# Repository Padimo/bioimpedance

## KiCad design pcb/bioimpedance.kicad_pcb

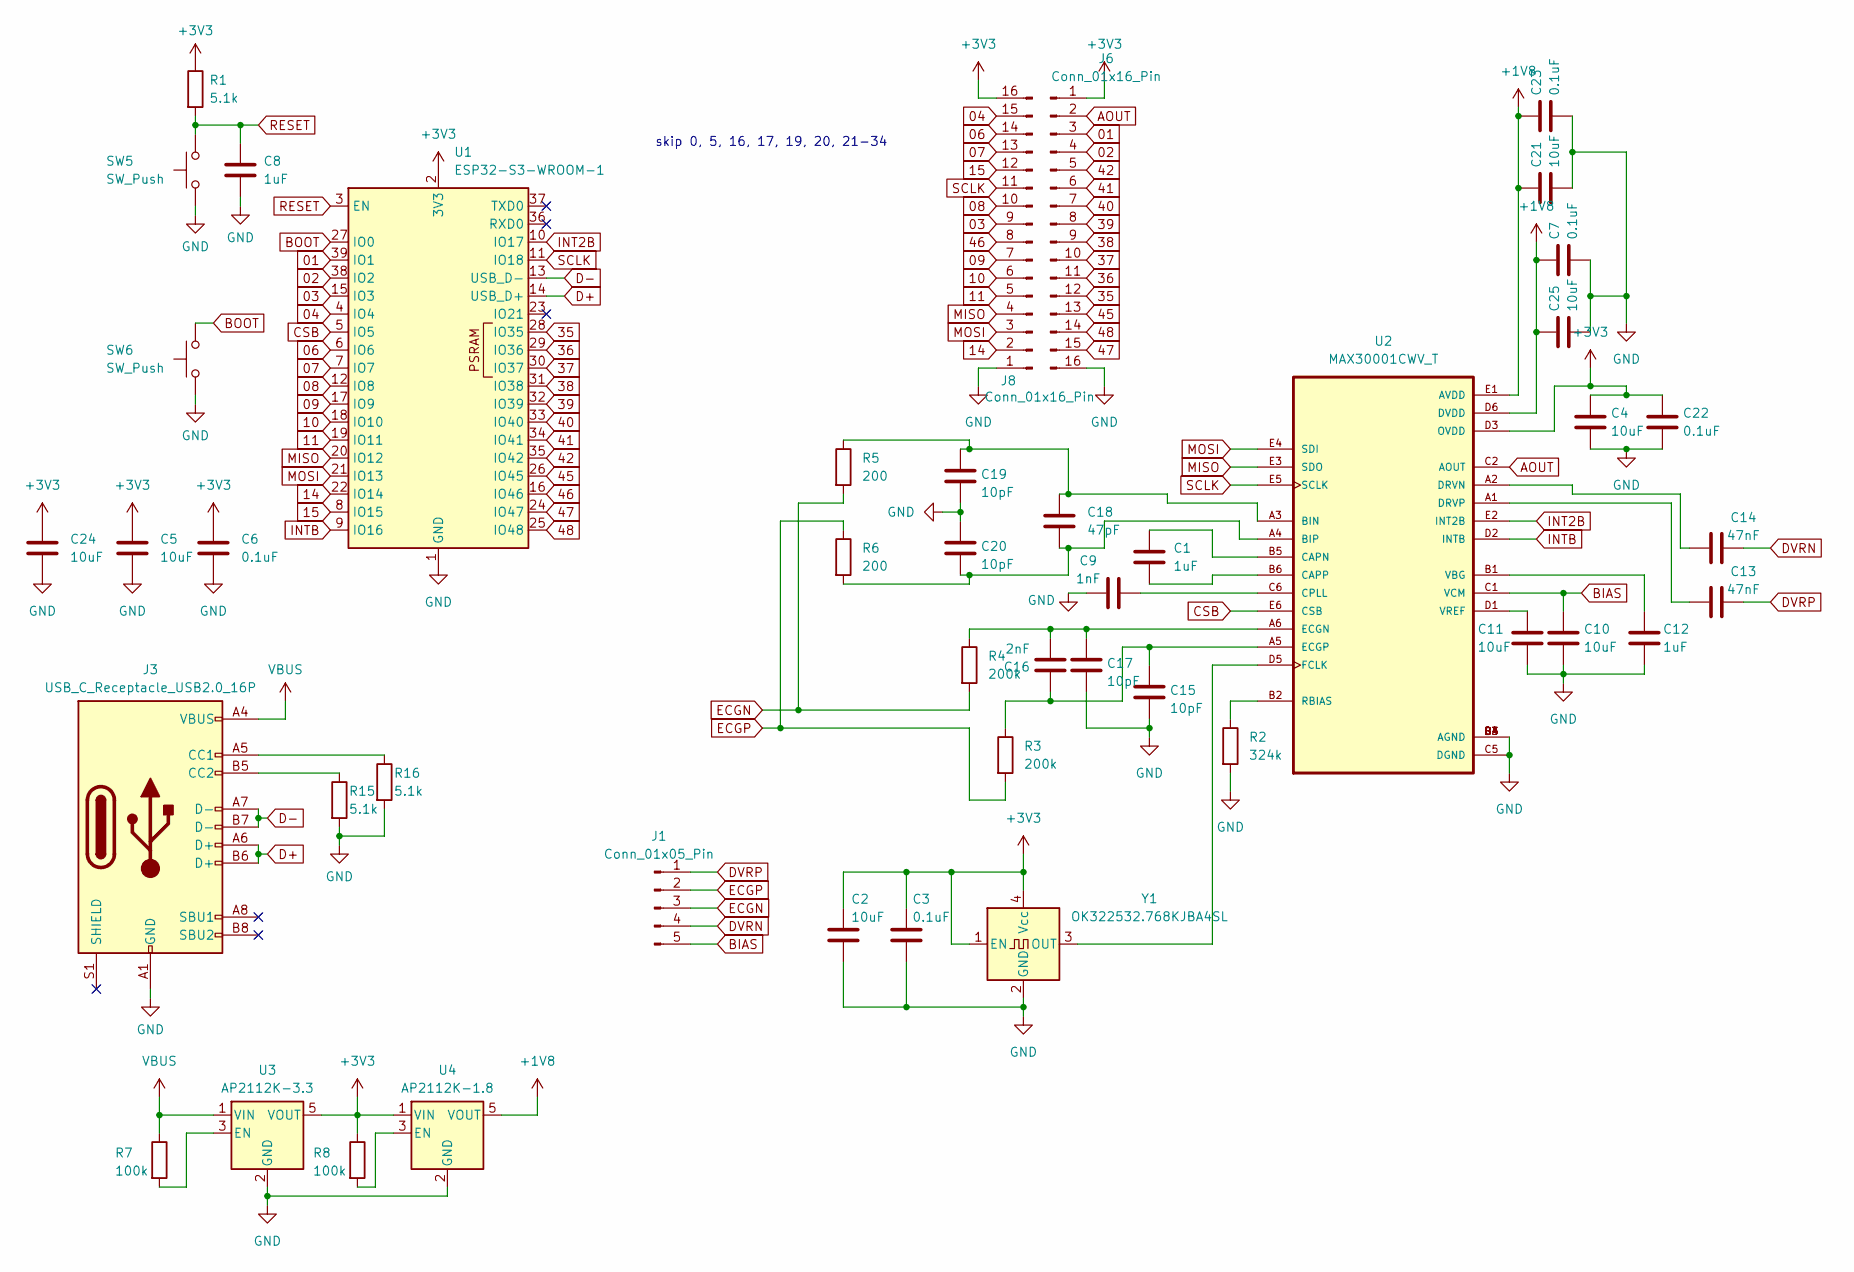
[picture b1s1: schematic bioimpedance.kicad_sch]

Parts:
C1, C8, C12: 1uF; C_0805_2012Metric
C2, C4, C5, C10, C11, C21, C24, C25: 10uF; C_0805_2012Metric
C3, C6, C7, C22, C23: 0.1uF; C_0805_2012Metric
C9: 1nF; C_0805_2012Metric
C13, C14: 47nF; C_0805_2012Metric
C15, C17, C19, C20: 10pF; C_0805_2012Metric
C16: 2nF; C_0805_2012Metric
C18: 47pF; C_0805_2012Metric
J1: Conn_01x05_Pin; PinHeader_1x05_P2.54mm_Vertical
J3: USB_C_Receptacle_USB2.0_16P; USB_C_Receptacle_GCT_USB4085
J6, J8: Conn_01x16_Pin; PinHeader_1x16_P2.54mm_Vertical
R1, R15, R16: 5.1k; R_0805_2012Metric
R2: 324k; R_0805_2012Metric
R3, R4: 200k; R_0805_2012Metric
R5, R6: 200; R_0805_2012Metric
R7, R8: 100k; R_0805_2012Metric
SW5, SW6: SW_Push; SW_Push_1P1T_NO_CK_KSC6xxJ
U1: ESP32-S3-WROOM-1
U2: MAX30001CWV_T; BGA30N50P5X6_274X292X69N
U3: AP2112K-3.3; SOT-23-5
U4: AP2112K-1.8; SOT-23-5
Y1: OK322532.768KJBA4SL; Crystal_SMD_3225-4Pin_3.2x2.5mm

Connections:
01: J6.3, U1.39 (IO1)
02: J6.4, U1.38 (IO2)
03: J8.9, U1.15 (IO3)
04: J8.15, U1.4 (IO4)
06: J8.14, U1.6 (IO6)
07: J8.13, U1.7 (IO7)
08: J8.10, U1.12 (IO8)
09: J8.7, U1.17 (IO9)
10: J8.6, U1.18 (IO10)
11: J8.5, U1.19 (IO11)
14: J8.2, U1.22 (IO14)
15: J8.12, U1.8 (IO15)
35: J6.12, U1.28 (IO35)
36: J6.11, U1.29 (IO36)
37: J6.10, U1.30 (IO37)
38: J6.9, U1.31 (IO38)
39: J6.8, U1.32 (IO39)
40: J6.7, U1.33 (IO40)
41: J6.6, U1.34 (IO41)
42: J6.5, U1.35 (IO42)
45: J6.13, U1.26 (IO45)
46: J8.8, U1.16 (IO46)
47: J6.15, U1.24 (IO47)
48: J6.14, U1.25 (IO48)
+1V8: C7.1, C21.1, C23.1, C25.1, U2.D6 (DVDD), U2.E1 (AVDD), U4.5 (VOUT)
+3V3: C2.1, C3.1, C4.1, C5.1, C6.1, C22.1, C24.1, J6.1, J8.16, R1.1, R8.1, U1.2 (3V3), U2.D3 (OVDD), U3.5 (VOUT), U4.1 (VIN), Y1.1 (EN), Y1.4 (Vcc)
AOUT: J6.2, U2.C2 (AOUT)
BIAS: C10.1, J1.5, U2.C1 (VCM)
BOOT: SW6.2, U1.27 (IO0)
CSB: U1.5 (IO5), U2.E6 (CSB)
D+: J3.A6 (D+), J3.B6 (D+), U1.14 (USB_D+)
D-: J3.A7 (D-), J3.B7 (D-), U1.13 (USB_D-)
DVRN: C14.2, J1.4
DVRP: C13.2, J1.1
ECGN: J1.3, R4.2, R5.2
ECGP: J1.2, R3.2, R6.1
GND: C2.2, C3.2, C4.2, C5.2, C6.2, C7.2, C8.2, C9.1, C10.2, C11.2, C12.2, C15.2, C17.2, C19.2, C20.1, C21.2, C22.2, C23.2, C24.2, C25.2, J3.A1 (GND), J3.A12 (GND), J3.B1 (GND), J3.B12 (GND), J6.16, J8.1, R2.2, R15.2, R16.2, SW5.1, SW6.1, U1.1 (GND), U1.40 (GND), U1.41 (GND), U2.B3 (AGND), U2.B4 (AGND), U2.C3 (AGND), U2.C4 (AGND), U2.C5 (DGND), U2.D4 (AGND), U3.2 (GND), U4.2 (GND), Y1.2 (GND)
INT2B: U1.10 (IO17), U2.E2 (INT2B)
INTB: U1.9 (IO16), U2.D2 (INTB)
MISO: J8.4, U1.20 (IO12), U2.E3 (SDO)
MOSI: J8.3, U1.21 (IO13), U2.E4 (SDI)
unnamed: J3.A5 (CC1), R16.1
unnamed: J3.B5 (CC2), R15.1
unnamed: C18.1, C19.1, R5.1, U2.A3 (BIN)
unnamed: C18.2, C20.2, R6.2, U2.A4 (BIP)
unnamed: C1.1, U2.B5 (CAPN)
unnamed: C1.2, U2.B6 (CAPP)
unnamed: C9.2, U2.C6 (CPLL)
unnamed: C14.1, U2.A2 (DRVN)
unnamed: C13.1, U2.A1 (DRVP)
unnamed: C16.2, C17.1, R4.1, U2.A6 (ECGN)
unnamed: C15.1, C16.1, R3.1, U2.A5 (ECGP)
unnamed: U2.D5 (FCLK), Y1.3 (OUT)
unnamed: R2.1, U2.B2 (RBIAS)
unnamed: C12.1, U2.B1 (VBG)
unnamed: C11.1, U2.D1 (VREF)
unnamed: R7.2, U3.3 (EN)
unnamed: R8.2, U4.3 (EN)
RESET: C8.1, R1.2, SW5.2, U1.3 (EN)
SCLK: J8.11, U1.11 (IO18), U2.E5 (SCLK)
VBUS: J3.A4 (VBUS), J3.A9 (VBUS), J3.B4 (VBUS), J3.B9 (VBUS), R7.1, U3.1 (VIN)

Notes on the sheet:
skip 0, 5, 16, 17, 19, 20, 21-34

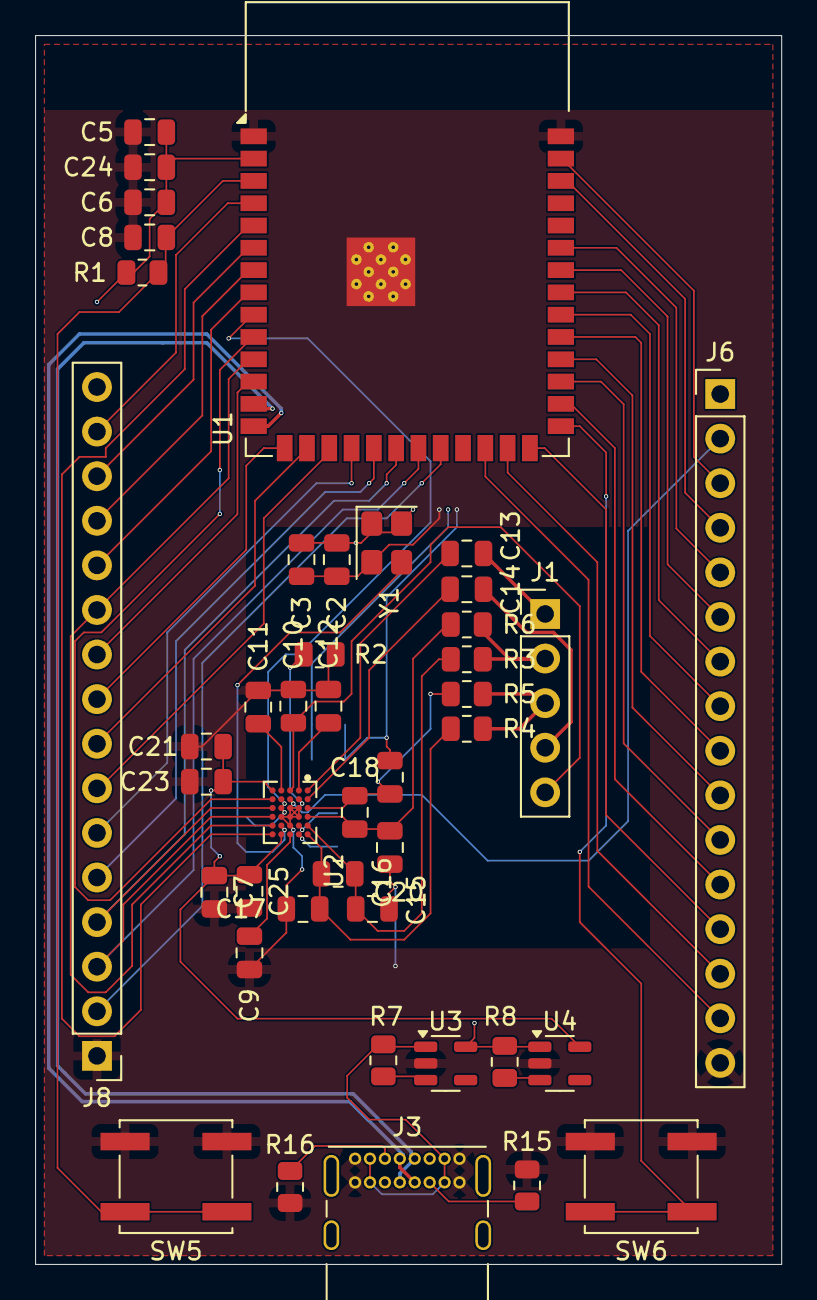
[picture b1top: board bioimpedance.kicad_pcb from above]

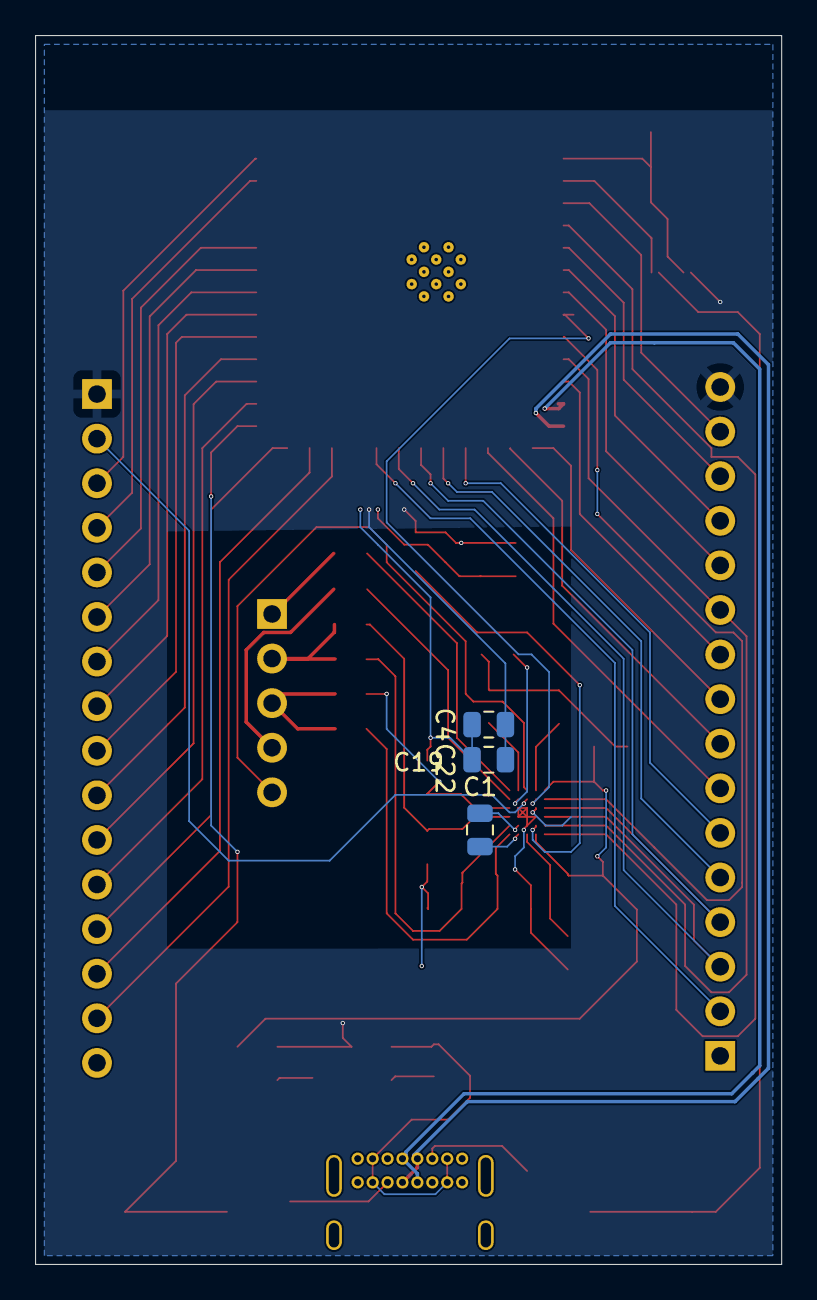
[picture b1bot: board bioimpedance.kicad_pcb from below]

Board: 2 copper layers, 42.5 x 70.0 mm, 46 parts (3 on the bottom side), 61 nets.

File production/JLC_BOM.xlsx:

Comment | Designator | Footprint | JLCPCB Part #（optional）
ESPRESSIF ESP32-S3-WROOM-1-N8 | U1 | ESP32-S3-WROOM-1 | C2913199
USB C | J3 | USB_C_Receptacle_GCT_USB4085 | C7095263
Push button | SW5,SW6 | SW_Push_1P1T_NO_CK_KSC6xxJ | C2888743
Oscillator 32kHz | Y1 | Crystal_SMD_3225_4Pin_3.2x2.5mm | C725996
MAX30001 | U2 | BGA30N50P5X6_274X292X69N | C2650384
1.8V regulator | U4 | SOT-25-5 | C176944
3.3V regulator | U3 | SOT-25-5 | C51118
10uF | C2,C4,C5,C10,C11,C21,C24,C25 |  | C1713
1uF | C1,C8,C12 |  | C1712
0.1uF | C3,C6,C7,C22,C23 |  | C1711
1nF | C9 |  | C46653
47nF | C13,C14 |  | C1744
2nF | C16 |  | C28260
47pF | C18 |  | C14857
10pF | C15,C17,C19,C20 |  | C107107
5.1k | R1,R15,R16 |  | C27834
324k | R2 |  | C17626
200k | R3,R4 |  | C17539
200 | R5,R6 |  | C17540
100k | R7,R8 |  | C25611

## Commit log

2025-08-16 update images
2025-08-18 reroute pcb
2025-08-18 reroute pcb AGAIN
2025-08-20 reroute board. again
2025-08-21 reroute board. again. removed copper near measurement traces
2025-08-31 updated journal
2025-11-13 Push all changes
